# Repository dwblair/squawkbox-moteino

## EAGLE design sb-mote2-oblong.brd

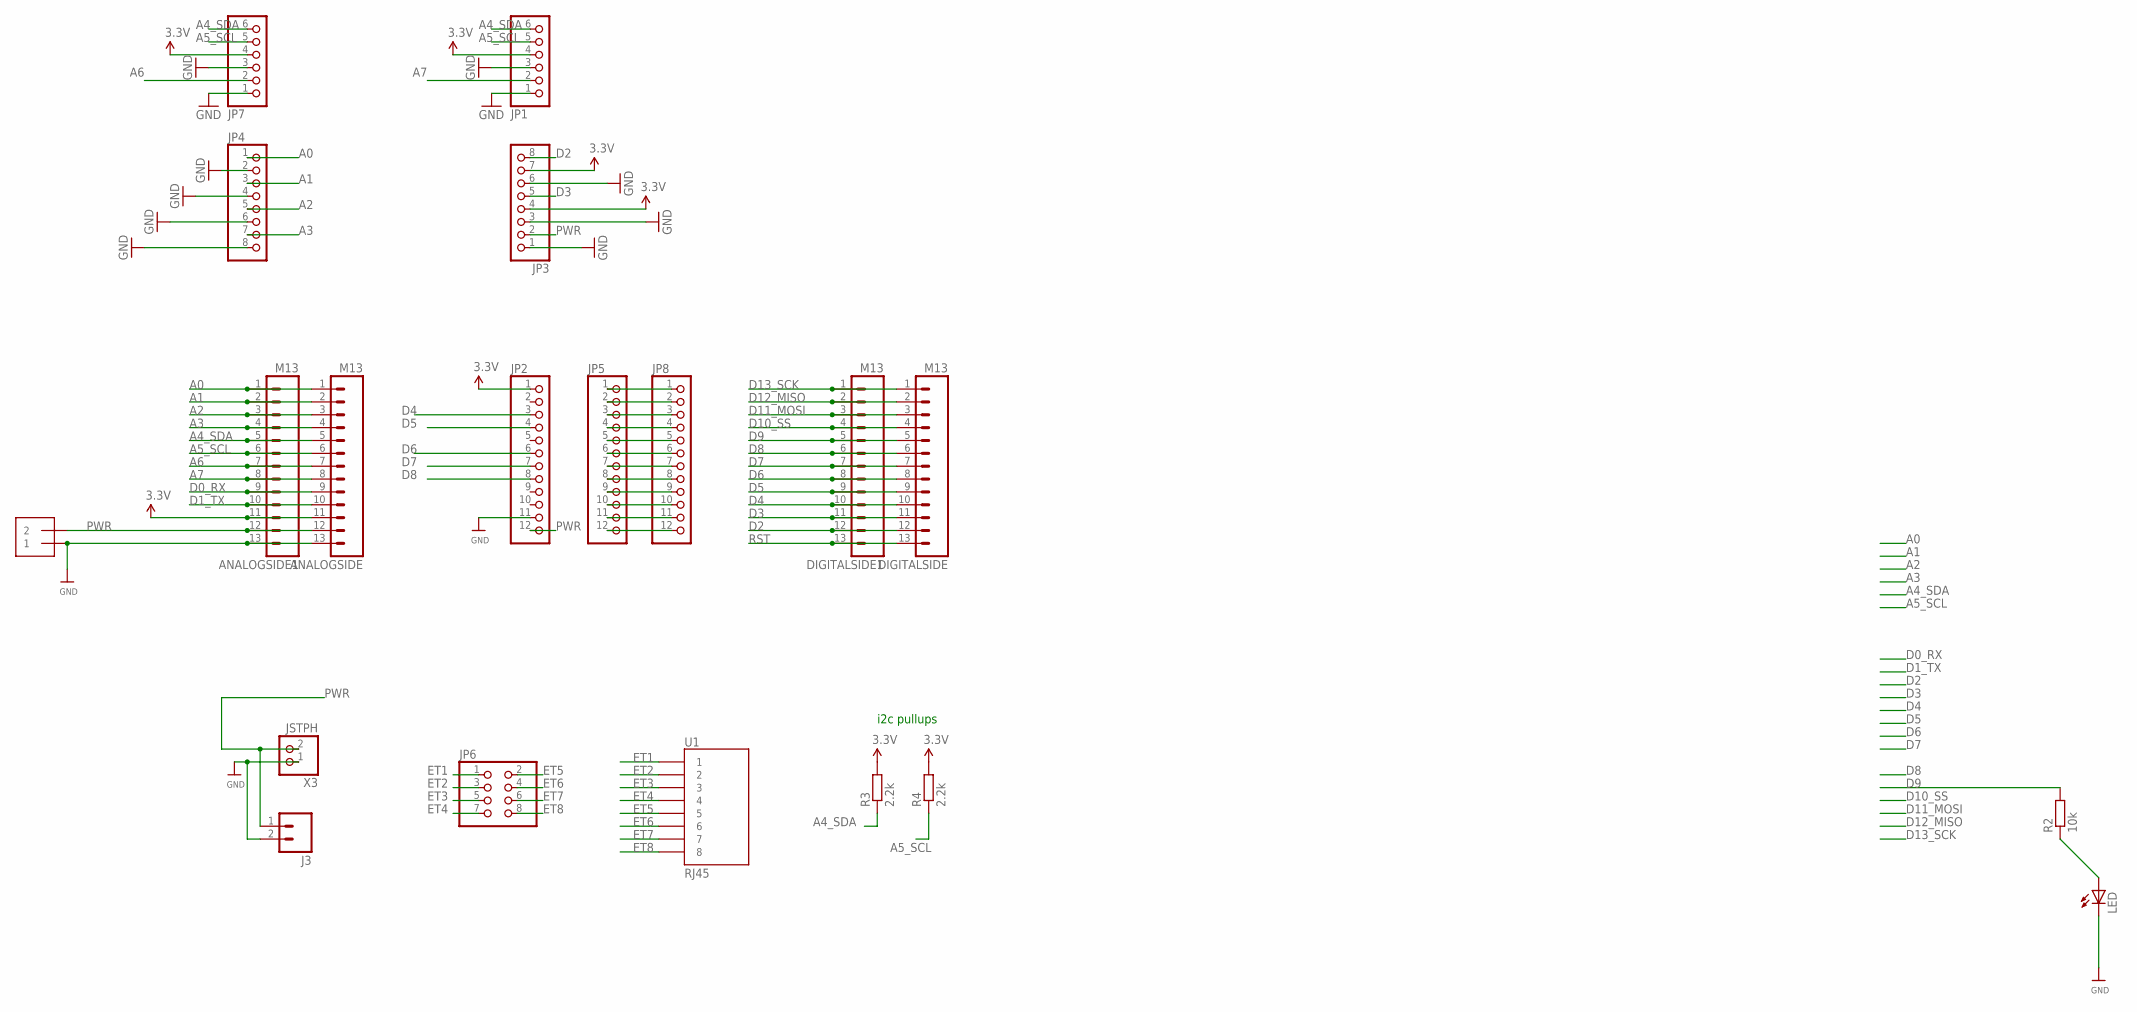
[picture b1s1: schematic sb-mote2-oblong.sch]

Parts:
ANALOGSIDE, ANALOGSIDE1: M13; 1X13
DIGITALSIDE, DIGITALSIDE1: M13; 1X13
J2: 1X2-3.5MM
J3: M02PTH; 1X02
JP1, JP7: PINHD-1X6-3.5MM; 1X06-3.5MM
JP2, JP5, JP8: PINHD-1X12-CB; 1X12-CB
JP3, JP4: PINHD-1X8-3.5MM; 1X08-3.5MM
JP6: PINHD-2X4; 2X04
LED: LED3MM
R2: 10k; 0204/7
R3, R4: 2.2k; 0204/7
U1: RJ45; RJ45-8
X3: JSTPH; JSTPH2

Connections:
A0: ANALOGSIDE.1, ANALOGSIDE1.1, JP4.1
A1: ANALOGSIDE.2, ANALOGSIDE1.2, JP4.3
A2: ANALOGSIDE.3, ANALOGSIDE1.3, JP4.5
A3: ANALOGSIDE.4, ANALOGSIDE1.4, JP4.7
A4_SDA: ANALOGSIDE.5, ANALOGSIDE1.5, JP1.6, JP7.6, R3.1
A5_SCL: ANALOGSIDE.6, ANALOGSIDE1.6, JP1.5, JP7.5, R4.1
A6: ANALOGSIDE.7, ANALOGSIDE1.7, JP7.2
A7: ANALOGSIDE.8, ANALOGSIDE1.8, JP1.2
D0_RX: ANALOGSIDE.9, ANALOGSIDE1.9
D1_TX: ANALOGSIDE.10, ANALOGSIDE1.10
D2: DIGITALSIDE.12, DIGITALSIDE1.12, JP3.8
D3: DIGITALSIDE.11, DIGITALSIDE1.11, JP3.5
D4: DIGITALSIDE.10, DIGITALSIDE1.10, JP2.3
D5: DIGITALSIDE.9, DIGITALSIDE1.9, JP2.4
D6: DIGITALSIDE.8, DIGITALSIDE1.8, JP2.6
D7: DIGITALSIDE.7, DIGITALSIDE1.7, JP2.7
D8: DIGITALSIDE.6, DIGITALSIDE1.6, JP2.8
D9: DIGITALSIDE.5, DIGITALSIDE1.5, R2.2
D10_SS: DIGITALSIDE.4, DIGITALSIDE1.4
D11_MOSI: DIGITALSIDE.3, DIGITALSIDE1.3
D12_MISO: DIGITALSIDE.2, DIGITALSIDE1.2
D13_SCK: DIGITALSIDE.1, DIGITALSIDE1.1
ET1: JP6.1, U1.1
ET2: JP6.3, U1.2
ET3: JP6.5, U1.3
ET4: JP6.7, U1.4
ET5: JP6.2, U1.5
ET6: JP6.4, U1.6
ET7: JP6.6, U1.7
ET8: JP6.8, U1.8
GND: ANALOGSIDE.13, ANALOGSIDE1.13, J2.1, J3.2, JP1.1, JP1.3, JP2.11, JP3.1, JP3.3, JP3.6, JP4.2, JP4.4, JP4.6, JP4.8, JP7.1, JP7.3, LED.K (C), X3.1
unnamed: JP5.1, JP8.1
unnamed: LED.A, R2.1
unnamed: JP5.2, JP8.2
unnamed: JP5.3, JP8.3
unnamed: JP5.4, JP8.4
unnamed: JP5.5, JP8.5
unnamed: JP5.6, JP8.6
unnamed: JP5.7, JP8.7
unnamed: JP5.8, JP8.8
unnamed: JP5.9, JP8.9
unnamed: JP5.10, JP8.10
unnamed: JP5.11, JP8.11
unnamed: JP5.12, JP8.12
PWR: ANALOGSIDE.12, ANALOGSIDE1.12, J2.2, J3.1, JP2.12, JP3.2, X3.2
RST: DIGITALSIDE.13, DIGITALSIDE1.13
SPEAKER2+: JP2.10
VCC: ANALOGSIDE.11, ANALOGSIDE1.11, JP1.4, JP2.1, JP3.4, JP3.7, JP7.4, R3.2, R4.2

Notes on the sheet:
i2c pullups

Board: 2 copper layers, 20 parts (1 on the bottom side), 47 nets, no tracks yet.

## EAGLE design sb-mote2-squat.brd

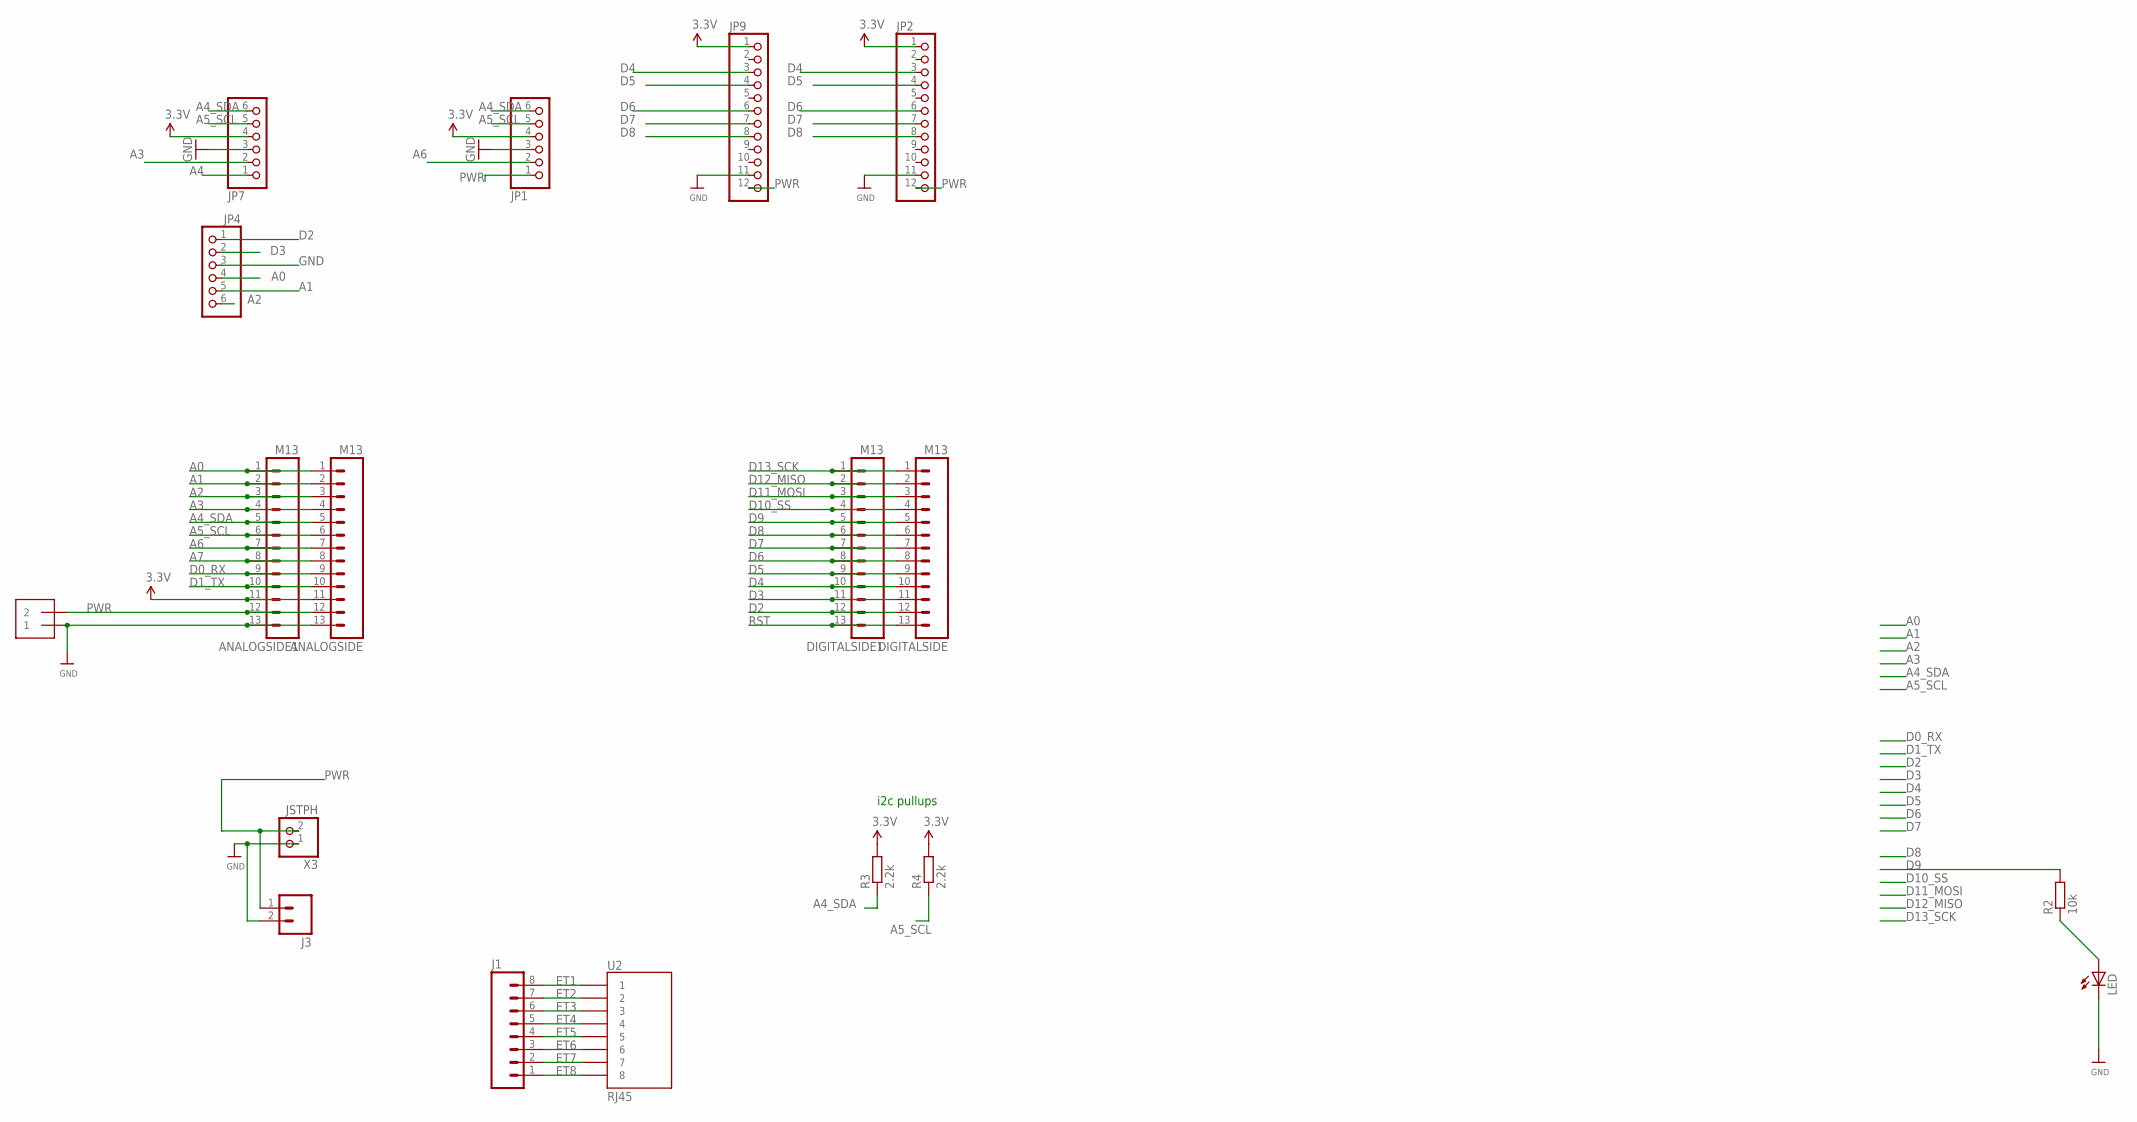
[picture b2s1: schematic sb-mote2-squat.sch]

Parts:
ANALOGSIDE, ANALOGSIDE1: M13; 1X13
DIGITALSIDE, DIGITALSIDE1: M13; 1X13
J1: M08; 1X08_ROUND
J2: 1X2-3.5MM
J3: M02PTH; 1X02
JP1, JP4, JP7: PINHD-1X6-3.5MM; 1X06-3.5MM
JP2, JP9: PINHD-1X12-CB; 1X12-CB
LED: LED3MM
R2: 10k; 0204/7
R3, R4: 2.2k; 0204/7
U2: RJ45; RJ45-8
X3: JSTPH; JSTPH2

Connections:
A0: ANALOGSIDE.1, ANALOGSIDE1.1, JP4.4
A1: ANALOGSIDE.2, ANALOGSIDE1.2, JP4.5
A2: ANALOGSIDE.3, ANALOGSIDE1.3, JP4.6
A3: ANALOGSIDE.4, ANALOGSIDE1.4, JP7.2
A4: JP7.1
A4_SDA: ANALOGSIDE.5, ANALOGSIDE1.5, JP1.6, JP7.6, R3.1
A5_SCL: ANALOGSIDE.6, ANALOGSIDE1.6, JP1.5, JP7.5, R4.1
A6: ANALOGSIDE.7, ANALOGSIDE1.7, JP1.2
A7: ANALOGSIDE.8, ANALOGSIDE1.8
D0_RX: ANALOGSIDE.9, ANALOGSIDE1.9
D1_TX: ANALOGSIDE.10, ANALOGSIDE1.10
D2: DIGITALSIDE.12, DIGITALSIDE1.12, JP4.1
D3: DIGITALSIDE.11, DIGITALSIDE1.11, JP4.2
D4: DIGITALSIDE.10, DIGITALSIDE1.10, JP2.3, JP9.3
D5: DIGITALSIDE.9, DIGITALSIDE1.9, JP2.4, JP9.4
D6: DIGITALSIDE.8, DIGITALSIDE1.8, JP2.6, JP9.6
D7: DIGITALSIDE.7, DIGITALSIDE1.7, JP2.7, JP9.7
D8: DIGITALSIDE.6, DIGITALSIDE1.6, JP2.8, JP9.8
D9: DIGITALSIDE.5, DIGITALSIDE1.5, R2.2
D10_SS: DIGITALSIDE.4, DIGITALSIDE1.4
D11_MOSI: DIGITALSIDE.3, DIGITALSIDE1.3
D12_MISO: DIGITALSIDE.2, DIGITALSIDE1.2
D13_SCK: DIGITALSIDE.1, DIGITALSIDE1.1
ET1: J1.8, U2.1
ET2: J1.7, U2.2
ET3: J1.6, U2.3
ET4: J1.5, U2.4
ET5: J1.4, U2.5
ET6: J1.3, U2.6
ET7: J1.2, U2.7
ET8: J1.1, U2.8
GND: ANALOGSIDE.13, ANALOGSIDE1.13, J2.1, J3.2, JP1.3, JP2.11, JP4.3, JP7.3, JP9.11, LED.K (C), X3.1
unnamed: LED.A, R2.1
PWR: ANALOGSIDE.12, ANALOGSIDE1.12, J2.2, J3.1, JP1.1, JP2.12, JP9.12, X3.2
RST: DIGITALSIDE.13, DIGITALSIDE1.13
SPEAKER2+: JP2.10
SPEAKER2+1: JP9.10
VCC: ANALOGSIDE.11, ANALOGSIDE1.11, JP1.4, JP2.1, JP7.4, JP9.1, R3.2, R4.2

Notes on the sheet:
i2c pullups

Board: 2 copper layers, 18 parts (1 on the bottom side), 35 nets, no tracks yet.

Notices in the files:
parts and their libraries:
SparkFun-Connectors: Licensing: CC v3.0 Share-Alike You are welcome to use this library for commercial purposes.
microbuilder: This work is placed in the public domain, and may be freely used for commercial and non-commercial work with the following conditions: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
